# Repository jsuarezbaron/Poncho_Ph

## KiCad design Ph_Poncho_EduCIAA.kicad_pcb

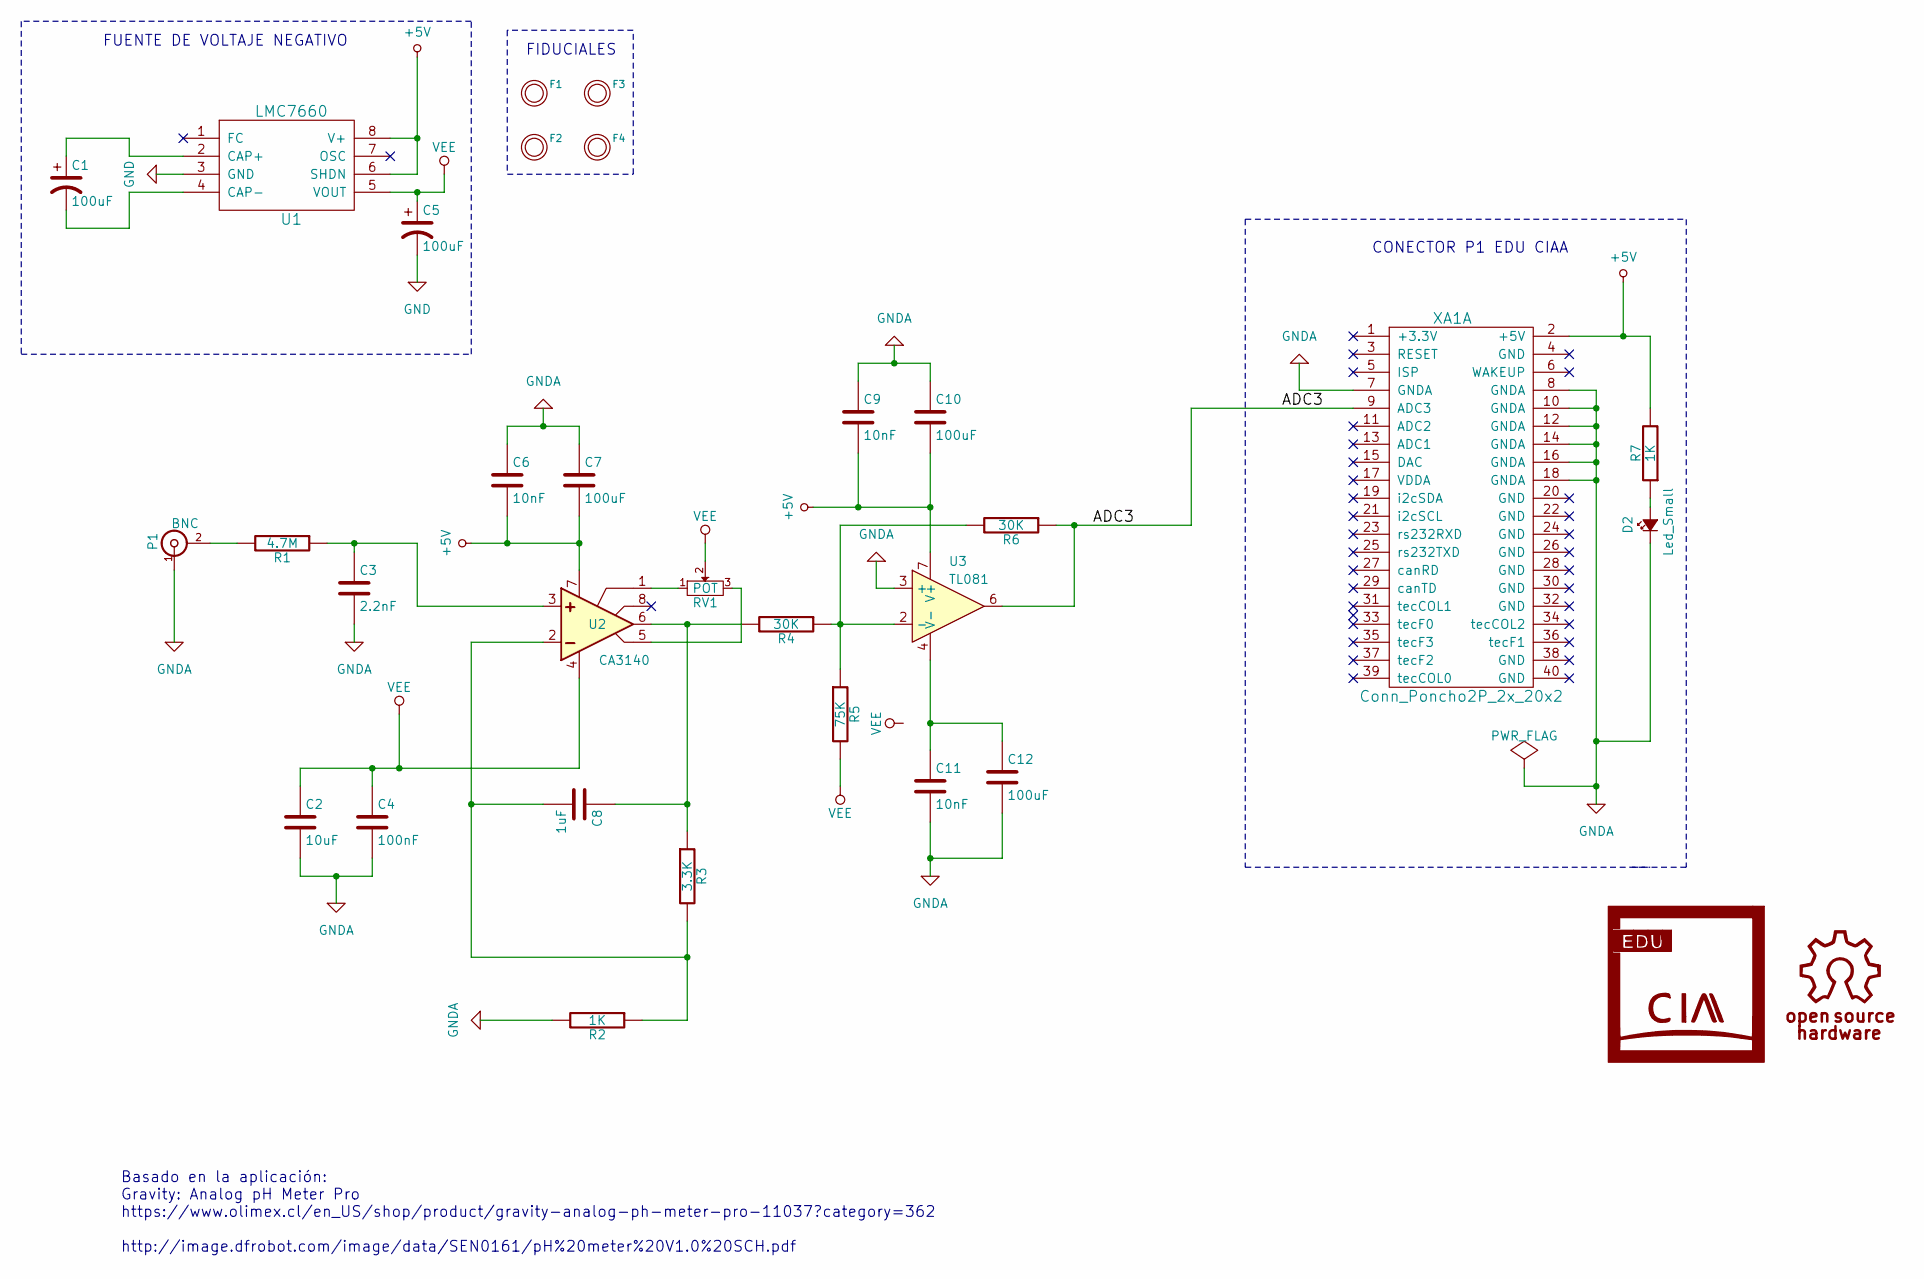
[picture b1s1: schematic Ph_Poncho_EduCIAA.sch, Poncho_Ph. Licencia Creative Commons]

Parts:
C1, C5: 100uF; CP_Elec_6.3x4.5; Mouser# UWT1V101MCL1GS; Digikey# 493-2203-1-ND
C2: 10uF; C_1206_HandSoldering; Mouser# 80-C1206C106J4R; Digikey# 399-9309-2-ND
C3: 2.2nF; C_1206_HandSoldering; Mouser# 581-12063A222JAT2; Digikey# 12063A222JAT2A-ND
C4: 100nF; C_1206_HandSoldering; Mouser# Value; Digikey# 478-1129-1-ND
C6, C9, C11: 10nF; C_1206_HandSoldering; Mouser# 81-GRM3195C1H103JA01; Digikey# 490-1754-2-ND
C7, C10, C12: 100uF; C_1206_HandSoldering; Mouser# 81-GRM31CR60J107KE9L; Digikey# 490-13982-1-ND
C8: 1uF; C_1206_HandSoldering; Mouser# 80-C1206C106J4R; Digikey# 399-9309-2-ND
D2: Led_Small; LED_1206; Mouser# Value; Digikey# 475-1410-2-ND
F1: FIDUCIAL; Fiducial_1mm; Mouser# Value; Digikey# Value
F2, F3, F4: FIDUCIAL; Fiducial_1mm
P1: BNC; BNC_Socket_TYCO-AMP; Mouser# 571-5227161-1; Digikey# A32244-ND
R1: 4.7M; R_1206_HandSoldering; Mouser# 603-RC1206JR-074M7L; Digikey# 311-4.7MERCT-ND
R2, R7: 1K; R_1206_HandSoldering; Mouser# Value; Digikey# 311-1.0KJRCT-ND
R3: 3.3K; R_1206_HandSoldering; Mouser# 603-RC1206JR-073K3L; Digikey# 311-3.3KERTR-ND
R4, R6: 30K; R_1206_HandSoldering; Mouser# 603-RC1206JR-0730KL; Digikey# 311-30KERCT-ND
R5: 75K; R_1206_HandSoldering; Mouser# 03-RC1206JR-0775KL; Digikey# 311-75KERCT-ND
RV1: POT; Potentiometer_Trimmer_Bourns_3296Y; Mouser# Value; Digikey# 39255K-ND
U1: LMC7660; SOIC-8-N; Mouser# LMC7660IMX/NOPB; Digikey# LMC7660IMX/NOPBCT-ND
U2: CA3140; SOIC-8-N; Mouser# 968-CA3140AEZ; Digikey# CA3140AEZ-ND
U3: TL081; SOIC-8-N; Mouser# 595-TL081CP; Digikey# 296-7203-5-ND
XA1: Conn_Poncho2P_2x_20x2; Conn_Poncho_Derecha; Mouser# 855-M50-3502042; Digikey# 952-1387-ND

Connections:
+5V: C6.2, C7.2, C9.2, C10.2, R7.2, U1.6 (SHDN), U1.8 (V+), U2.7 (V+), U3.7 (V+), XA1.2 (+5V)
/ADC3: R6.1, U3.6, XA1.9 (ADC3)
GND: C5.2, U1.3 (GND)
GNDA: C2.2, C3.2, C4.2, C6.1, C7.1, C9.1, C10.1, C11.2, C12.2, D2.1 (K), P1.1 (In), R2.2, U3.3 (+), XA1.7 (GNDA), XA1.8 (GNDA), XA1.10 (GNDA), XA1.12 (GNDA), XA1.14 (GNDA), XA1.16 (GNDA), XA1.18 (GNDA)
unnamed: C1.1, U1.2 (CAP+)
unnamed: C1.2, U1.4 (CAP-)
unnamed: C3.1, R1.1, U2.3 (NON)
unnamed: C8.1, R3.1, R4.2, U2.6 (OUTPUT)
unnamed: C8.2, R2.1, R3.2, U2.2 (INVERTING)
unnamed: C11.1, C12.1, U3.4 (V-)
unnamed: D2.2 (A), R7.1
unnamed: P1.2 (Ext), R1.2
unnamed: R4.1, R5.1, R6.2, U3.2 (-)
unnamed: RV1.1, U2.1 (BAL/COMP)
unnamed: RV1.3, U2.5 (BALANCE)
VEE: C2.1, C4.1, C5.1, R5.2, RV1.2, U1.5 (VOUT), U2.4 (V-)

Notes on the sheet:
FUENTE DE VOLTAJE NEGATIVO
Basado en la aplicación: Gravity: Analog pH Meter Pro https://www.olimex.cl/en_US/shop/product/gravity-analog-ph-meter-pro-11037?category=362 http://image.dfrobot.com/image/data/SEN0161/pH%20meter%20V1.0%20SCH.pdf
FIDUCIALES
CONECTOR P1 EDU CIAA

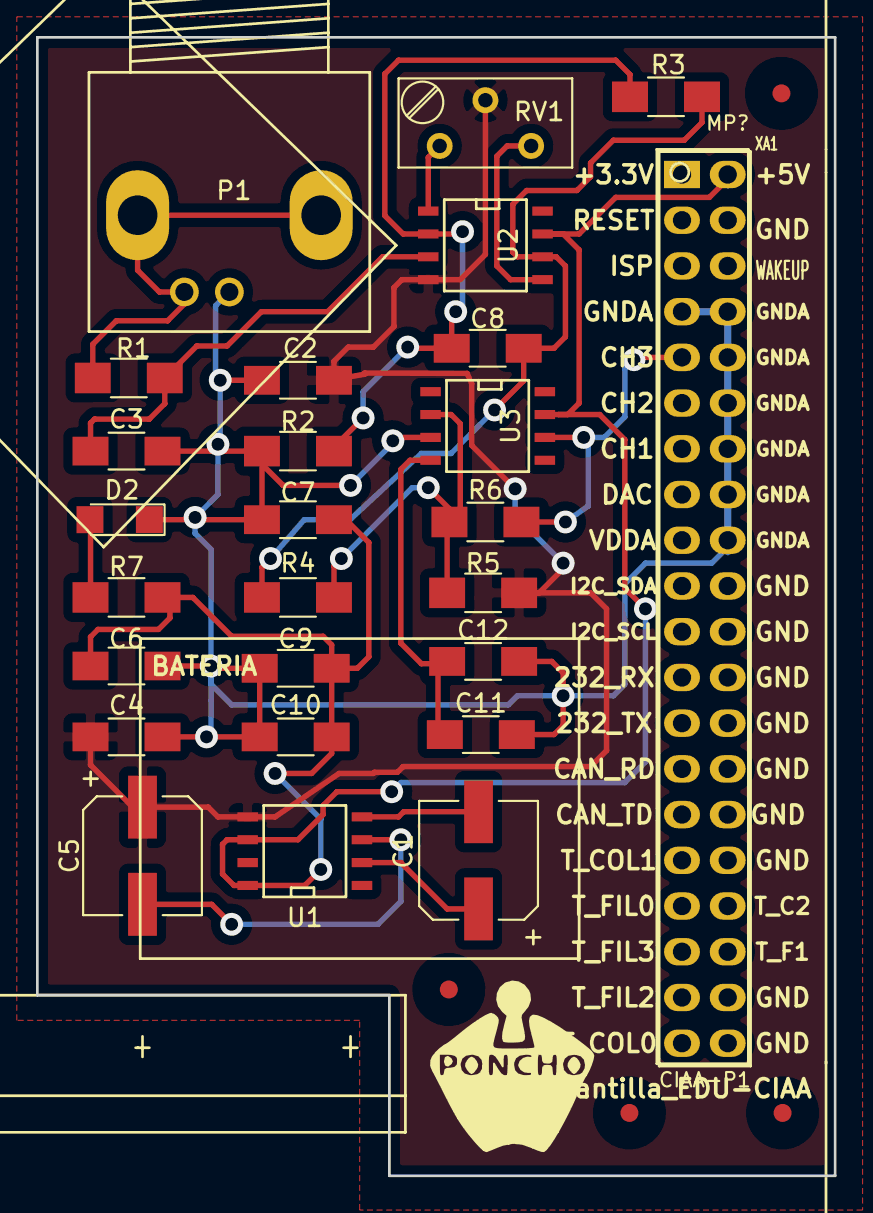
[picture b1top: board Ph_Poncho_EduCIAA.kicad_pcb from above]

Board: 2 copper layers, 44.3 x 63.2 mm, 33 parts (0 on the bottom side), 16 nets.

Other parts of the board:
G101: Logo_OSHWA
MP?: Plantilla_EDU-CIAA
XA?: Plantilla_Poncho_Derecha

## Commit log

2017-05-10 Poncho_PhV1.0
2017-05-10 Subiendo Doc
2017-05-10 Subiendo 3D.3dshapes
2017-05-10 Subiendo Ph_Poncho.pretty
2017-05-10 Subiendo Ph_Poncho_EduCIAA-cache.lib
2017-05-10 Ph_Poncho_EduCIAA.bak
2017-05-10 Ph_Poncho_EduCIAA.kicad_pcb
2017-05-10 Subiendo Ph_Poncho_EduCIAA.pro
2017-05-10 Subiendo Ph_Poncho_EduCIAA.sch
2017-05-10 Subiendo Ph_Poncholibs
2017-05-10 Subiendo TC1121COA.sym
2017-06-26 Se cambió el inversor de voltaje TC1121COA por el LMC7660
2017-06-26 Se agrega nuevo .net
2017-06-26 Se agregan las notas de ingeniería
2017-06-26 Se agregan las hojas de datos
2017-07-16 Agregando footprints del poncho
2017-07-17 Subiendo Hojas de datos
2017-07-17 Se agrega planilla de revisiones
2017-07-17 Se agrega nueva netlist
2017-07-17 Nueva versión del .pro
2017-07-17 Nueva versión de esquemático
2017-07-22 Agregando el ruteo del PCB
2017-07-22 Se modificaron algunas pistas
2017-07-22 Modificación de pistas
2017-08-12 Subiendo modificaciones, correcciones y primera versión de la placa ruteada y con planos de tierra
